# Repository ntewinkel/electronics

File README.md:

# electronics
This repository contains source code, schematics, and diagrams related to my projects.

Most of these projects will have complete blog posts and explanations on element14.com

Please feel free to use it as you wish (thus the MIT license)

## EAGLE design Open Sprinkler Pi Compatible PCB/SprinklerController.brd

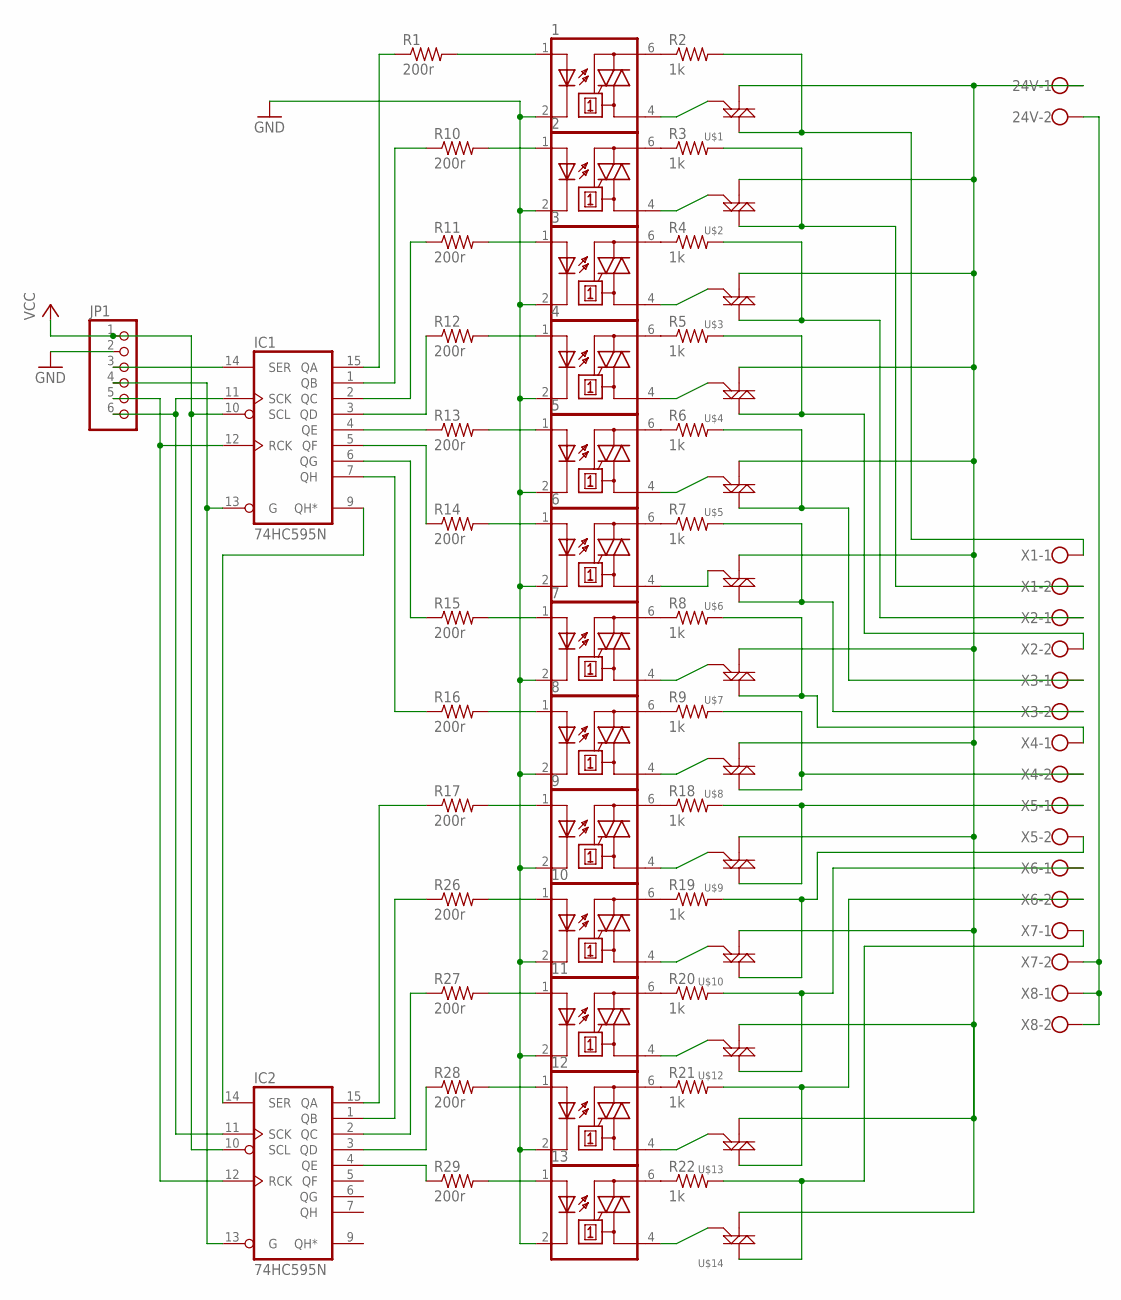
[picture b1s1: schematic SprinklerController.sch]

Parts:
1, 2, 3, 4, 5, 6, 7, 8, 9, 10, 11, 12, 13: MOC3021M; DIL06
24V: W237-102
IC1, IC2: 74HC595N; DIL16
JP1: PINHD-1X6; 1X06
R1, R10, R11, R12, R13, R14, R15, R16, R17, R26, R27, R28, R29: 200r; 0204/7
R2, R3, R4, R5, R6, R7, R8, R9, R18, R19, R20, R21, R22: 1k; 0204/7
U$1, U$2, U$3, U$4, U$5, U$6, U$7, U$8, U$9, U$10, U$12, U$13, U$14: TRIACPTH; TO-92
X1, X2, X3, X4, X5, X6, X7, X8: W237-102

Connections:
GND: 1.2 (C), 2.2 (C), 3.2 (C), 4.2 (C), 5.2 (C), 6.2 (C), 7.2 (C), 8.2 (C), 9.2 (C), 10.2 (C), 11.2 (C), 12.2 (C), 13.2 (C), IC1.8 (GND), IC2.8 (GND), JP1.2
unnamed: IC1.12 (RCK), IC2.12 (RCK), JP1.5
unnamed: IC1.14 (SER), JP1.3
unnamed: IC1.13 (G), IC2.13 (G), JP1.4
unnamed: 1.4 (A1), U$1.2 (G)
unnamed: IC1.11 (SCK), IC2.11 (SCK), JP1.6
unnamed: R19.2, U$10.3 (M2), X5.2
unnamed: R2.2, U$1.3 (M2), X1.1
unnamed: 24V.1, U$1.1 (M1), U$2.1 (M1), U$3.1 (M1), U$4.1 (M1), U$5.1 (M1), U$6.1 (M1), U$7.1 (M1), U$8.1 (M1), U$9.1 (M1), U$10.1 (M1), U$12.1 (M1), U$13.1 (M1), U$14.1 (M1)
unnamed: 1.1 (A), R1.2
unnamed: IC1.9 (QH*), IC2.14 (SER)
unnamed: IC1.7 (QH), R16.1
unnamed: 1.6 (A2), R2.1
unnamed: 2.6 (A2), R3.1
unnamed: 3.6 (A2), R4.1
unnamed: 4.6 (A2), R5.1
unnamed: 5.6 (A2), R6.1
unnamed: 6.6 (A2), R7.1
unnamed: 7.6 (A2), R8.1
unnamed: 8.6 (A2), R9.1
unnamed: 10.4 (A1), U$10.2 (G)
unnamed: 24V.2, X7.2, X8.1, X8.2
unnamed: 13.4 (A1), U$14.2 (G)
unnamed: 12.4 (A1), U$13.2 (G)
unnamed: 11.4 (A1), U$12.2 (G)
unnamed: R4.2, U$3.3 (M2), X2.1
unnamed: R5.2, U$4.3 (M2), X2.2
unnamed: R6.2, U$5.3 (M2), X3.1
unnamed: R7.2, U$6.3 (M2), X3.2
unnamed: R8.2, U$7.3 (M2), X4.1
unnamed: 2.1 (A), R10.2
unnamed: 9.4 (A1), U$9.2 (G)
unnamed: 3.1 (A), R11.2
unnamed: 4.1 (A), R12.2
unnamed: R9.2, U$8.3 (M2), X4.2
unnamed: 5.1 (A), R13.2
unnamed: 6.1 (A), R14.2
unnamed: 7.1 (A), R15.2
unnamed: 8.1 (A), R16.2
unnamed: IC1.6 (QG), R15.1
unnamed: IC1.5 (QF), R14.1
unnamed: IC1.4 (QE), R13.1
unnamed: IC1.3 (QD), R12.1
unnamed: IC1.2 (QC), R11.1
unnamed: IC1.1 (QB), R10.1
unnamed: 8.4 (A1), U$8.2 (G)
unnamed: IC1.15 (QA), R1.1
unnamed: IC2.4 (QE), R29.1
unnamed: 9.6 (A2), R18.1
unnamed: 10.6 (A2), R19.1
unnamed: 11.6 (A2), R20.1
unnamed: 12.6 (A2), R21.1
unnamed: 13.6 (A2), R22.1
unnamed: 7.4 (A1), U$7.2 (G)
unnamed: 6.4 (A1), U$6.2 (G)
unnamed: 5.4 (A1), U$5.2 (G)
unnamed: 4.4 (A1), U$4.2 (G)
unnamed: 3.4 (A1), U$3.2 (G)
unnamed: 2.4 (A1), U$2.2 (G)
unnamed: R20.2, U$12.3 (M2), X6.1
unnamed: R21.2, U$13.3 (M2), X6.2
unnamed: R22.2, U$14.3 (M2), X7.1
unnamed: R3.2, U$2.3 (M2), X1.2
unnamed: R18.2, U$9.3 (M2), X5.1
unnamed: 9.1 (A), R17.2
unnamed: 10.1 (A), R26.2
unnamed: 11.1 (A), R27.2
unnamed: 12.1 (A), R28.2
unnamed: 13.1 (A), R29.2
unnamed: IC2.15 (QA), R17.1
unnamed: IC2.1 (QB), R26.1
unnamed: IC2.2 (QC), R27.1
unnamed: IC2.3 (QD), R28.1
VCC: IC1.10 (SCL), IC1.16 (VCC), IC2.10 (SCL), IC2.16 (VCC), JP1.1

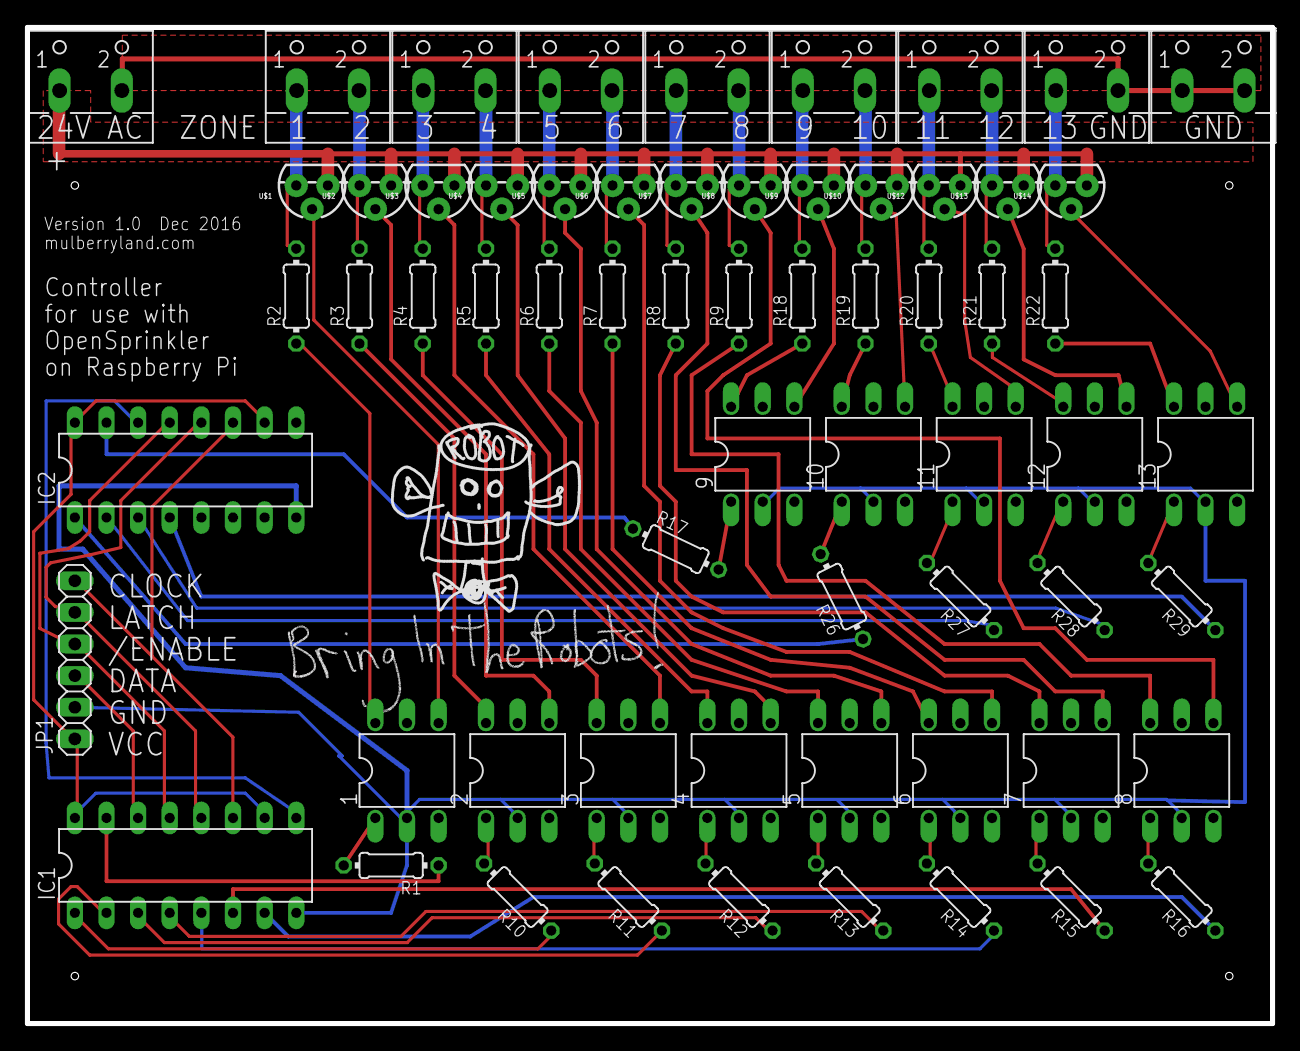
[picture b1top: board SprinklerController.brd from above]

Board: 2 copper layers, 100.0 x 80.0 mm, 64 parts (0 on the bottom side), 74 nets.

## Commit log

2017-05-26 Readme updated
    Updated description
2017-05-26 IOT2020 pond filler sketches
    Added sketches for my IOT2020 pond filler project
2017-05-28 Added Schematics
    Added Schematics
2017-05-28 Added water probes test
    Added water probes test sketch.
2017-05-28 removed blink sketch
    Removed blink sketch. It was added accidentally (it’s just the basic
    Arduino Blink sketch)
2017-05-28 Updated pullup resistor values
    Updated pullup resistor values - they should be more like 4 M-Ohm.
2017-12-28 Added Sprinkler controller PCB designs
    Added Sprinkler controller PCB designs. Uses EAGLE.
2017-12-28 Added Clausometer
    Added Clausometer project.
2018-02-14 Added ESP8266 Examples
2018-04-13 add all files required for the project
2018-04-13 fixed dependency on unused input file
2018-04-27 Added missing files
2018-05-01 Added Arduino Torch Relay
2018-05-01 Updated to allow graphing of specified sensor
2018-10-07 added door monitoring project
2018-10-07 Added project description
2018-10-07 formatting update
2018-10-08 Changed to use D3, as D4 has the LED connected to it.
2019-01-02 Added ConnectedXMasTrees project
2019-01-05 Changed pin use, updated motion time, updated to look for sensor high.
2019-01-12 Changed GPIO pins used; Added startup flashes
2019-01-12 Added schematics (Fritzing)
2019-03-03 Updated Readme file
2019-03-03 Added Multi-sensor logging example.
2019-03-03 Updated comments

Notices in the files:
parts and their libraries:
SparkFun-DiscreteSemi: Licensing: Creative Commons ShareAlike 4.0 International - https://creativecommons.org/licenses/by-sa/4.0
